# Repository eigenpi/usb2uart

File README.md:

# USB to UART Converter

## Short Description

Design files (KiCAD layout, Arduino testing program, and 3D printing files of 
enclosure in Fusion 360) of a USB to UART converter.

## Details

This repository contains all design files of a USB to UART converter.
The design uses the popular FT232R FTDI chip and its layout was created with
with KiCAD 6.0. The 3D CAD model was created with Autodesk Oct.2022, the free
educators/students version.

All the important design steps that you may want to follow to replicate this
project are described in several youtube videos. This project was split in these 
steps on purpose in order to help students learn for the first time KiCAD layout, 
how to reflow, solder, test, and print a 3D enclosure.

1. [Part 1: Introduction and Objectives](https://www.youtube.com/watch?v=YGBzahBK7fY)

2. [Part 2: Install Software and Design Considerations](https://www.youtube.com/watch?v=YuMDFhPcvQs)

3. [Part 3: Schematic Entry (or Capture)](https://www.youtube.com/watch?v=v7kIc4Z1D-g)

4. [Part 4: Footprint Assignment and Netlist Generation](https://www.youtube.com/watch?v=86rWFbxiwfI)

5. [Part 5: Placement](https://www.youtube.com/watch?v=sIsJZZ_kQxs)

6. [Part 6: Routing](https://www.youtube.com/watch?v=J2sLzAaGzOM)

7. [Part 7: Soldering](https://www.youtube.com/watch?v=Kl9dPHJpTGs)

8. [Part 8: Testing and Programming an Arduino Pro Mini](https://www.youtube.com/watch?v=vrjB3BWouZs)

9. [Part 9: 3D Printed Enclosure Designed in Autodesk Fusion 360](https://youtu.be/6EWKOvSFG48)

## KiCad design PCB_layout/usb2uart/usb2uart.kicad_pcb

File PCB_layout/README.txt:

usb2uart/ project folder created with KiCAD 6.0

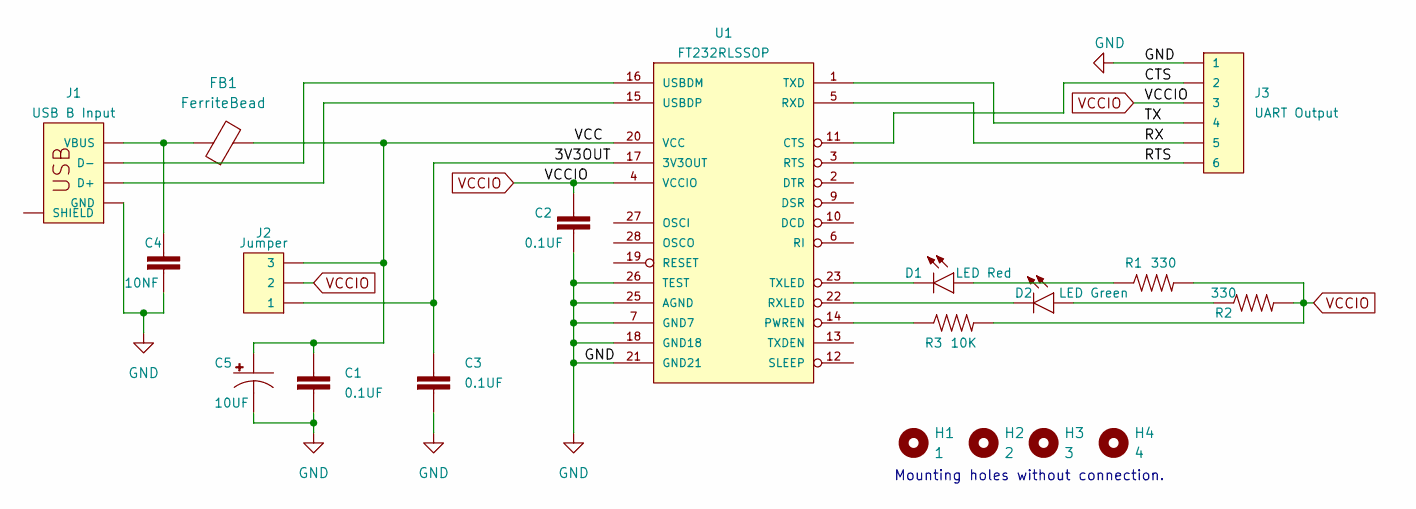
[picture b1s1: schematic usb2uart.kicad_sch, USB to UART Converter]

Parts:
C1, C2, C3: 0.1UF; CAP-PTH-5MM
C4: 10NF; CAP-PTH-5MM
C5: 10UF; CPOL-RADIAL-5MM-10MM
D1: LED Red; LED_3MM
D2: LED Green; LED_3MM
FB1: FerriteBead; LairdTech_28C0236-0JW-10
H1: 1; STANDOFF_GROUNDING
H2: 2; STANDOFF_GROUNDING
H3: 3; STANDOFF_GROUNDING
H4: 4; STANDOFF_GROUNDING
J1: USB B Input; USB-B-PTH
J2: Jumper; 1X03
J3: UART Output; 1X06
R1, R2: 330; AXIAL-0.3
R3: 10K; AXIAL-0.3-KIT
U1: FT232RLSSOP; SSOP28DB

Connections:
/3V3OUT: C3.1, J2.1, U1.17 (3V3OUT)
/CTS: J3.2, U1.11 (CTS)
/RTS: J3.6, U1.3 (RTS)
/RX: J3.5, U1.5 (RXD)
/TX: J3.4, U1.1 (TXD)
/VCC: C1.1, C5.+, FB1.2, J2.3, U1.20 (VCC)
GND: C1.2, C2.2, C3.2, C4.2, C5.-, J1.GND, J3.1, U1.7 (GND7), U1.18 (GND18), U1.21 (GND21), U1.25 (AGND), U1.26 (TEST)
unnamed: C4.1, FB1.1, J1.VBUS
unnamed: D1.A, R1.P$1 (1)
unnamed: D1.K (C), U1.23 (TXLED)
unnamed: D2.A, R2.P$1 (1)
unnamed: D2.K (C), U1.22 (RXLED)
unnamed: R3.P$1 (1), U1.14 (PWREN)
unnamed: J1.D+, U1.15 (USBDP)
unnamed: J1.D-, U1.16 (USBDM)
VCCIO: C2.1, J2.2, J3.3, R1.P$2 (2), R2.P$2 (2), R3.P$2 (2), U1.4 (VCCIO)

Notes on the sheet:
Mounting holes without connection.

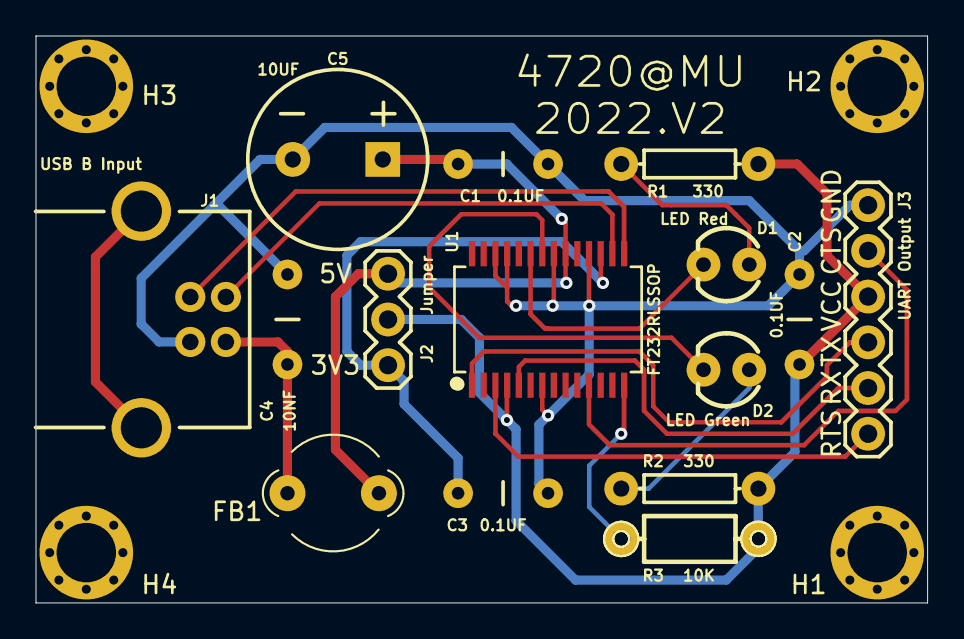
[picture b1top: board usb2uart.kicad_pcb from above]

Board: 2 copper layers, 49.5 x 31.5 mm, 19 parts (0 on the bottom side), 16 nets.
